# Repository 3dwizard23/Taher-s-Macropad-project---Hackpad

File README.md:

# Taher-s-Macropad-project---Hackpad
My first time attempting something of the kind . I had to learn how to do things like create a PCB , understand how to use applications like autodesk and kicad , but it was fun and didnt take too long

I personally Havent exactly mastered using autodesk for my cad since this was my first time creating something on the app , so i couldnt figure out how to import the parts successfully as the computer just couldnt find them . 

I started this project initially when i saw a tiktok about the project and how hackclub were trying to create a engineering community or sorts and joined to try and learn something new

BOM 

My project features 
SK6812 MINI-E LEDs (x2)
EC11 Rotary encoders ( 2x)
MX-Style switches (4x)
1x XIAO RP2040
1x Case- two 3d printed parts 
M3x16mm screws 
M3x5mx4mm heatset inserts

My firmware is really basic since i dont know much python and really used this project to learn some , i also did have to use some help from the basic starter code in kmk that the tutorial suggests and some use of ai but it should work

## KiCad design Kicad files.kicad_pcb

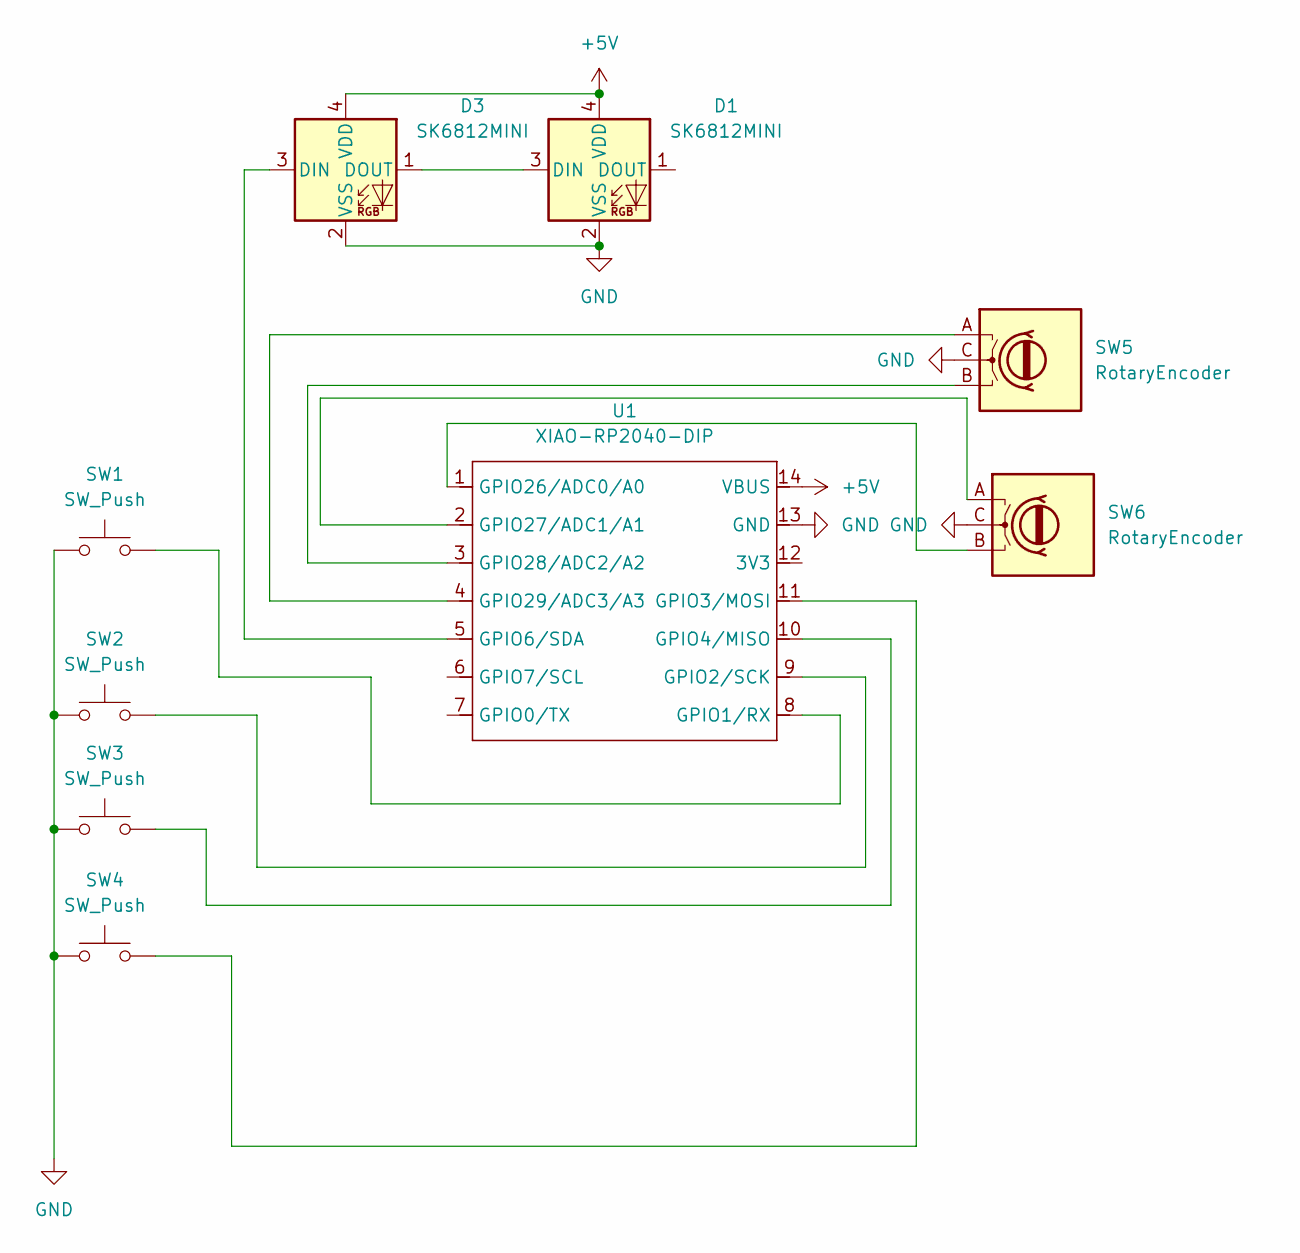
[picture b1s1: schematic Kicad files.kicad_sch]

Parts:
D1, D3: SK6812MINI; LED_SK6812MINI_PLCC4_3.5x3.5mm_P1.75mm
SW1, SW2, SW3, SW4: SW_Push; SW_Cherry_MX_1.00u_PCB
SW5, SW6: RotaryEncoder; RotaryEncoder_Alps_EC11E-Switch_Vertical_H20mm
U1: XIAO-RP2040-DIP

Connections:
+5V: D1.4 (VDD), D3.4 (VDD), U1.14 (VBUS)
GND: D1.2 (VSS), D3.2 (VSS), SW1.1, SW2.1, SW3.1, SW4.1, SW5.C, SW6.C, U1.13 (GND)
unnamed: D1.3 (DIN), D3.1 (DOUT)
unnamed: D3.3 (DIN), U1.5 (GPIO6/SDA)
unnamed: SW1.2, U1.8 (GPIO1/RX)
unnamed: SW2.2, U1.9 (GPIO2/SCK)
unnamed: SW4.2, U1.11 (GPIO3/MOSI)
unnamed: SW3.2, U1.10 (GPIO4/MISO)
unnamed: SW6.B, U1.1 (GPIO26/ADC0/A0)
unnamed: SW6.A, U1.2 (GPIO27/ADC1/A1)
unnamed: SW5.B, U1.3 (GPIO28/ADC2/A2)
unnamed: SW5.A, U1.4 (GPIO29/ADC3/A3)

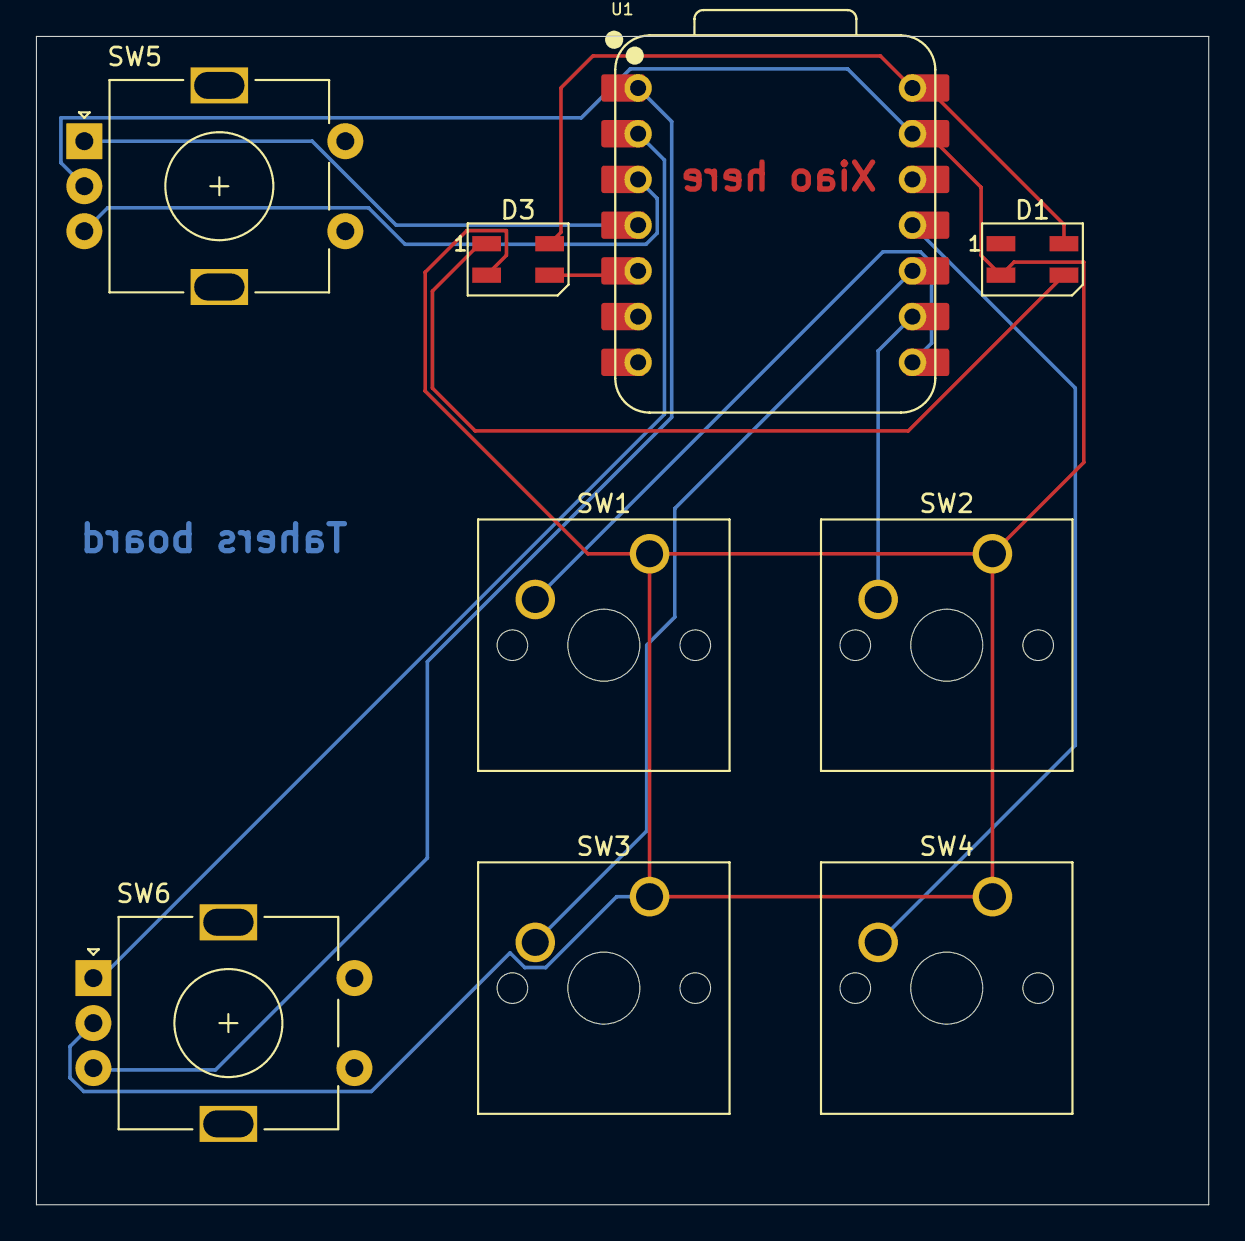
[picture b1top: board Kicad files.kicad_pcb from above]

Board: 2 copper layers, 65.1 x 64.9 mm, 9 parts (0 on the bottom side), 12 nets.

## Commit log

2026-01-06 Create Firmware _ kmk
2026-01-07 Rename kicad_pro.txt to KIcad files
    _pro _sch _pcb
2026-01-07 Create Cadmodel
2026-01-07 add macropad project files
